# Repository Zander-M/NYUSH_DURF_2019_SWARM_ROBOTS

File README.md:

# NYUSH_DURF_2019_SWARM_ROBOTS

For project logs, please visit [<https://hackaday.io/project/165119-nyu-shanghai-swarm-robot-systemhackaday.io/>] for project log and other stuff.

Project Code is in the Project/Code/ folder.  
Project Note is in the Project/Note/ folder.

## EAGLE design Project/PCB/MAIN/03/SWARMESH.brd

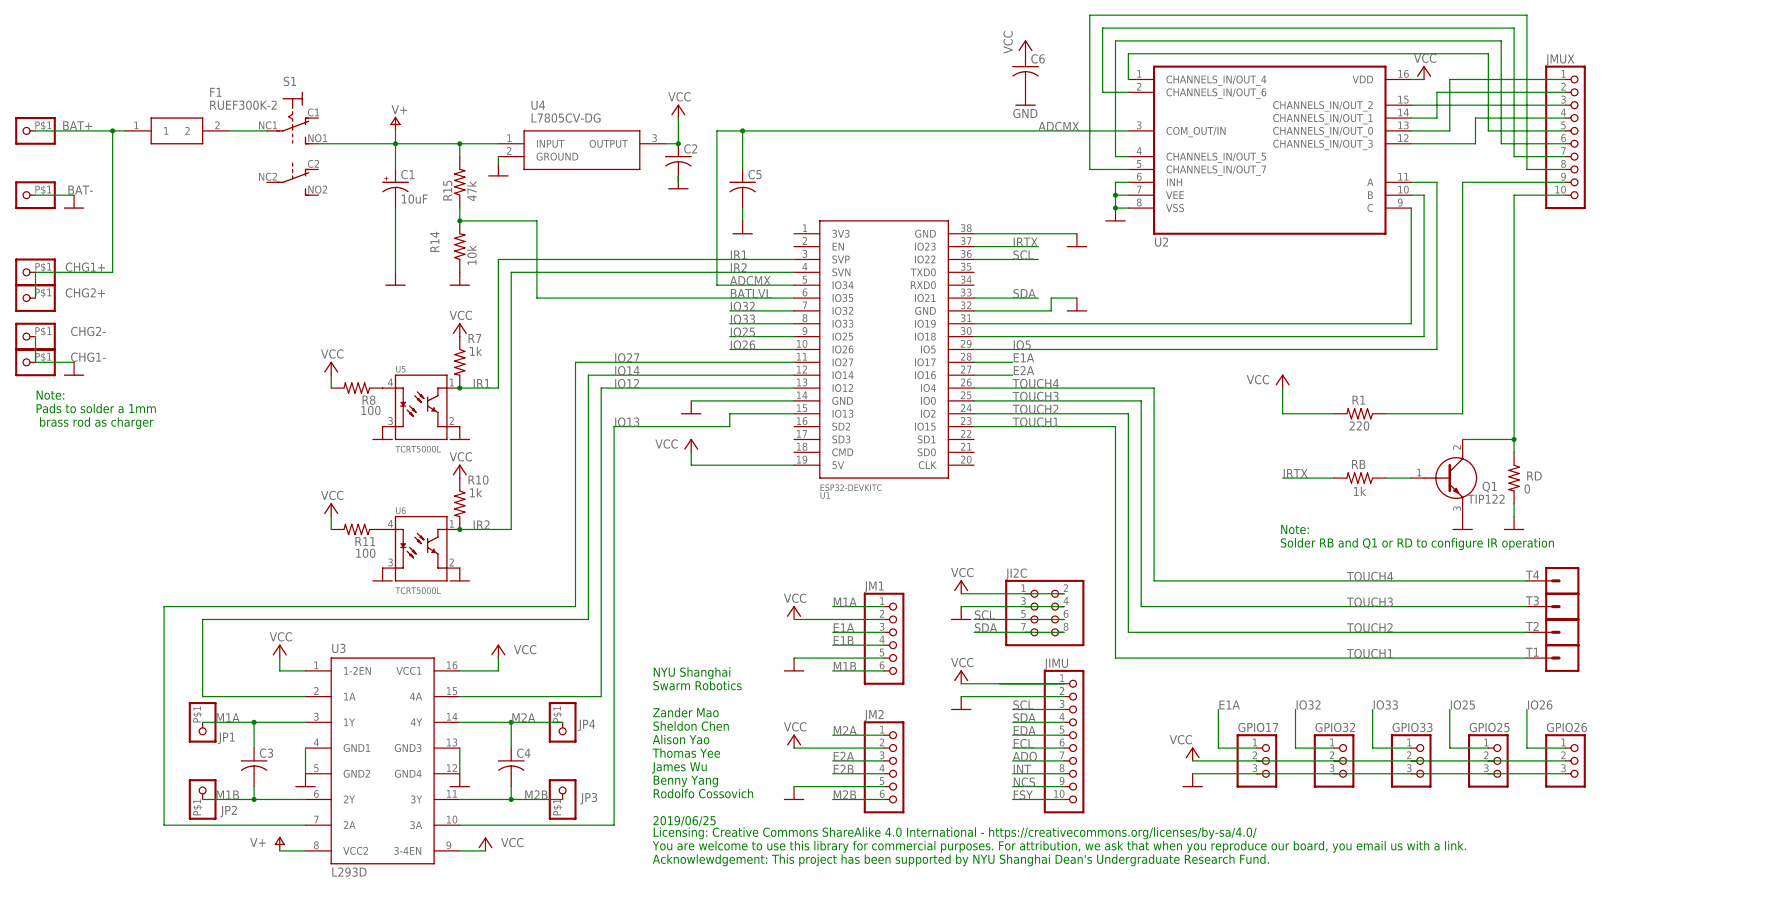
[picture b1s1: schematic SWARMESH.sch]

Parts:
BAT+: PINHD-1X1-BIGPOGO; 1X1-BIGPOGO
BAT-: PINHD-1X1-BIGPOGO; 1X1-BIGPOGO
C1: 10uF; E2-5
C2, C5: C-US025-030X050; C025-030X050
C3, C4, C6: C-US025-025X050; C025-025X050
CHG1+, CHG1-, CHG2+, CHG2-: PINHD-1X1-BIGPOGO; 1X1-BIGPOGO
F1: RUEF300K-2; RUEF300K2
GPIO17, GPIO25, GPIO26, GPIO32, GPIO33: PINHD-1X3; 1X03
JI2C: PINHD-2X4; 2X04
JIMU: PINHD-1X10; 1X10-BIG
JM1, JM2: PINHD-1X6; 1X06
JMUX: PINHD-1X10; 1X10-BIG
JP1, JP2, JP3, JP4: PINHD-1X1-BIGPOGO; 1X1-BIGPOGO
Q1: TIP122; TO270P460X1020X2008-3P
R1: 220; 0207/9
R7, R10: 1k; 0207/9
R8, R11: 100; 0207/9
R14: 10k; 0207/9
R15: 47k; 0207/9
RB: 1k; 0207/9
RD: 0; 0207/9
S1: SWITCH_320-938; PS22F03
T1, T2, T3, T4: CONN_01SPRING-CONN; SPRING-CONNECTOR
U1: ESP32DEVKITC; ESP32-DEVKITC
U2: CD4051BEE4; CD4051BEE4DIP
U3: L293D; DIL16
U4: L7805CV-DG; TO270P460X1020X2008-3P
U5, U6: TCRT5000L; XDCR_TCRT5000L

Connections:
ADCMX: C5.1, U1.5 (IO34), U2.3 (COM_OUT/IN)
ADO: JIMU.7
BATLVL: R14.2, R15.1, U1.6 (IO35)
E1A: GPIO17.1, JM1.3, U1.28 (IO17)
E1B: JM1.4
E2A: JM2.3, U1.27 (IO16)
E2B: JM2.4
ECL: JIMU.6
EDA: JIMU.5
FSY: JIMU.10
GND: BAT-.P$1, C1.-, C2.2, C5.2, C6.2, CHG1-.P$1, CHG2-.P$1, GPIO17.3, GPIO25.3, GPIO26.3, GPIO32.3, GPIO33.3, JI2C.3, JI2C.4, JIMU.2, JM1.5, JM2.5, Q1.3 (E), R14.1, RD.2, U1.14 (GND), U1.32 (GND), U1.38 (GND), U3.4 (GND1), U3.5 (GND2), U3.12 (GND4), U3.13 (GND3), U4.2 (GROUND), U5.2 (E), U5.3 (C), U6.2 (E), U6.3 (C)
INT: JIMU.8
IO5: U1.29 (IO5), U2.11 (A)
IO12: U1.13 (IO12), U3.15 (4A)
IO13: U1.15 (IO13), U3.10 (3A)
IO14: U1.12 (IO14), U3.2 (1A)
IO25: GPIO25.1, U1.9 (IO25)
IO26: GPIO26.1, U1.10 (IO26)
IO27: U1.11 (IO27), U3.7 (2A)
IO32: GPIO32.1, U1.7 (IO32)
IO33: GPIO33.1, U1.8 (IO33)
IR1: R7.2, U1.3 (SVP), U5.1 (CO)
IR2: R10.2, U1.4 (SVN), U6.1 (CO)
IRTX: RB.2, U1.37 (IO23)
M1A: C3.1, JM1.1, JP1.P$1, U3.3 (1Y)
M1B: C3.2, JM1.6, JP2.P$1, U3.6 (2Y)
M2A: C4.1, JM2.1, JP4.P$1, U3.14 (4Y)
M2B: C4.2, JM2.6, JP3.P$1, U3.11 (3Y)
unnamed: JMUX.6, U2.4 (CHANNELS_IN/OUT_5)
unnamed: U1.30 (IO18), U2.10 (B)
unnamed: U1.31 (IO19), U2.9 (C)
unnamed: R11.1, U6.4 (A)
unnamed: R8.1, U5.4 (A)
unnamed: JMUX.5, U2.1 (CHANNELS_IN/OUT_4)
unnamed: Q1.1 (B), RB.1, U2.6 (INH), U2.7 (VEE), U2.8 (VSS)
unnamed: JMUX.7, U2.2 (CHANNELS_IN/OUT_6)
unnamed: JMUX.8, U2.5 (CHANNELS_IN/OUT_7)
unnamed: BAT+.P$1, CHG1+.P$1, CHG2+.P$1, F1.1
unnamed: JMUX.9, R1.1
unnamed: JMUX.10, Q1.2 (C), RD.1
unnamed: F1.2, S1.NC1
unnamed: JMUX.1, U2.13 (CHANNELS_IN/OUT_0)
unnamed: JMUX.2, U2.14 (CHANNELS_IN/OUT_1)
unnamed: JMUX.4, U2.12 (CHANNELS_IN/OUT_3)
unnamed: JMUX.3, U2.15 (CHANNELS_IN/OUT_2)
NCS: JIMU.9
SCL: JI2C.5, JI2C.6, JIMU.3, U1.36 (IO22)
SDA: JI2C.7, JI2C.8, JIMU.4, U1.33 (IO21)
TOUCH1: T1.P$2, U1.23 (IO15)
TOUCH2: T2.P$2, U1.24 (IO2)
TOUCH3: T3.P$2, U1.25 (IO0)
TOUCH4: T4.P$2, U1.26 (IO4)
V+: C1.+, R15.2, S1.NO1 (S), U3.8 (VCC2), U4.1 (INPUT)
VCC: C2.1, C6.1, GPIO17.2, GPIO25.2, GPIO26.2, GPIO32.2, GPIO33.2, JI2C.1, JI2C.2, JIMU.1, JM1.2, JM2.2, R1.2, R7.1, R8.2, R10.1, R11.2, U1.19 (5V), U2.16 (VDD), U3.1 (1-2EN), U3.9 (3-4EN), U3.16 (VCC1), U4.3 (OUTPUT)

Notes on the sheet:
NYU Shanghai Swarm Robotics Zander Mao Sheldon Chen Alison Yao Thomas Yee James Wu Benny Yang Rodolfo Cossovich 2019/06/25
Licensing: Creative Commons ShareAlike 4.0 International - https://creativecommons.org/licenses/by-sa/4.0/ You are welcome to use this library for commercial purposes. For attribution, we ask that when you reproduce our board, you email us with a link. Acknowlewdgement: This project has been suppor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
Note: Solder RB and Q1 or RD to configure IR operation
Note: Pads to solder a 1mm brass rod as charger

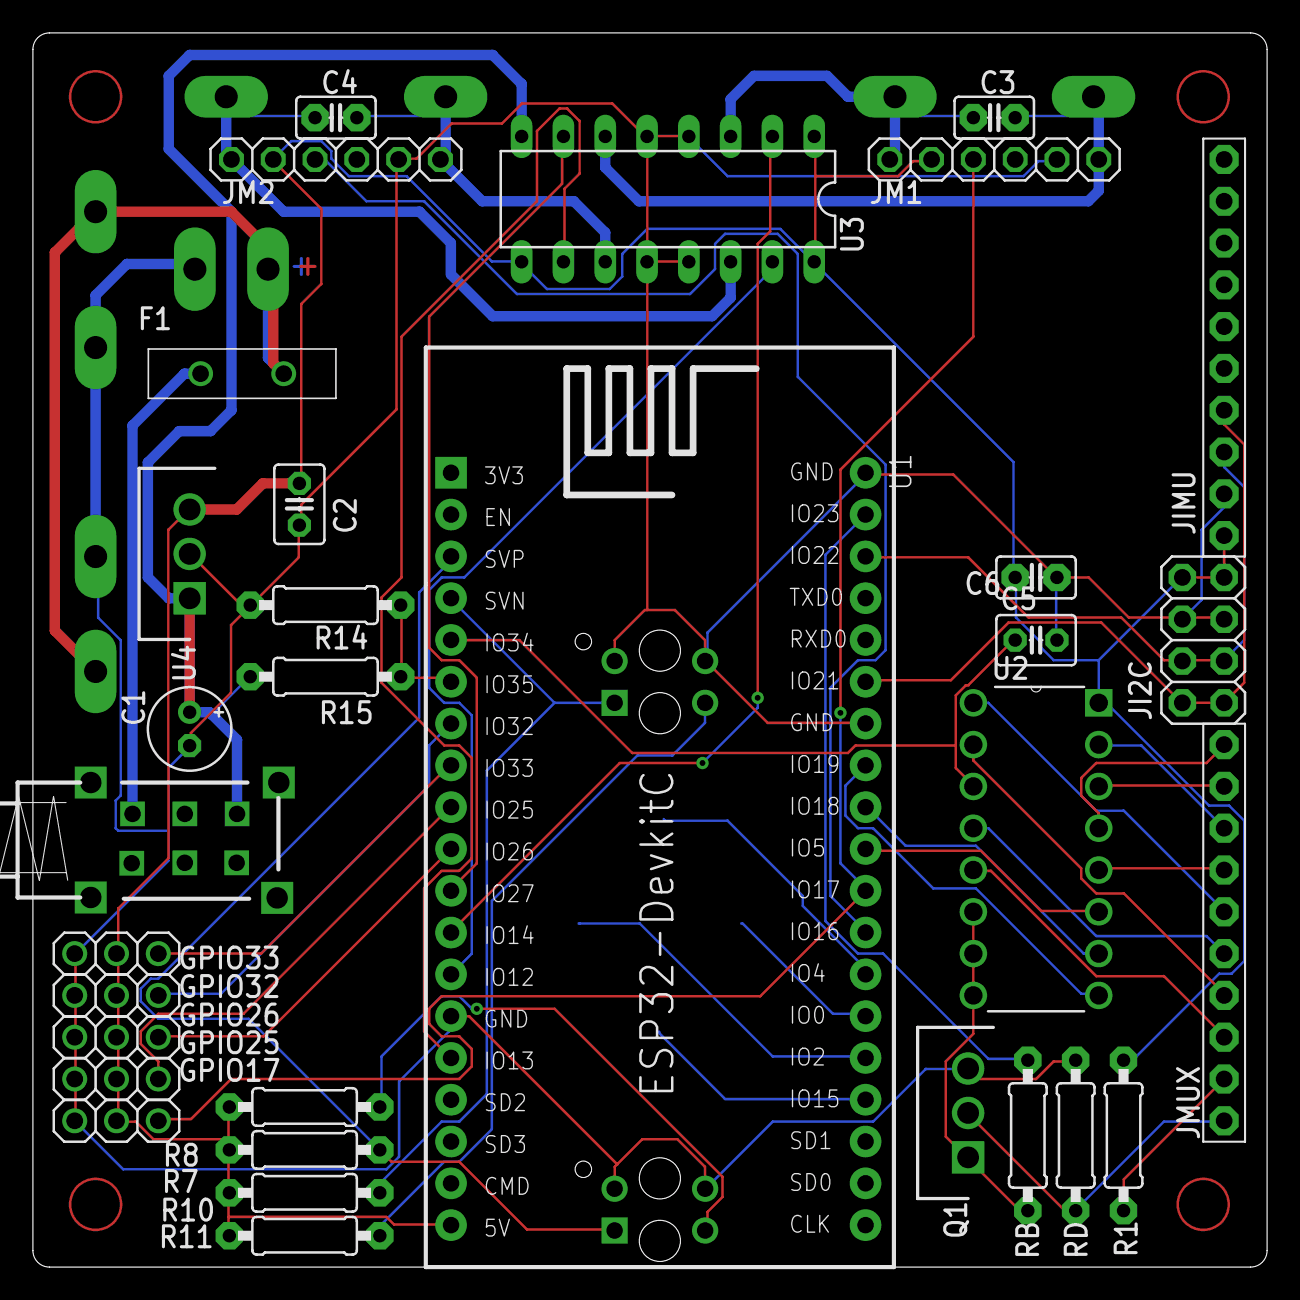
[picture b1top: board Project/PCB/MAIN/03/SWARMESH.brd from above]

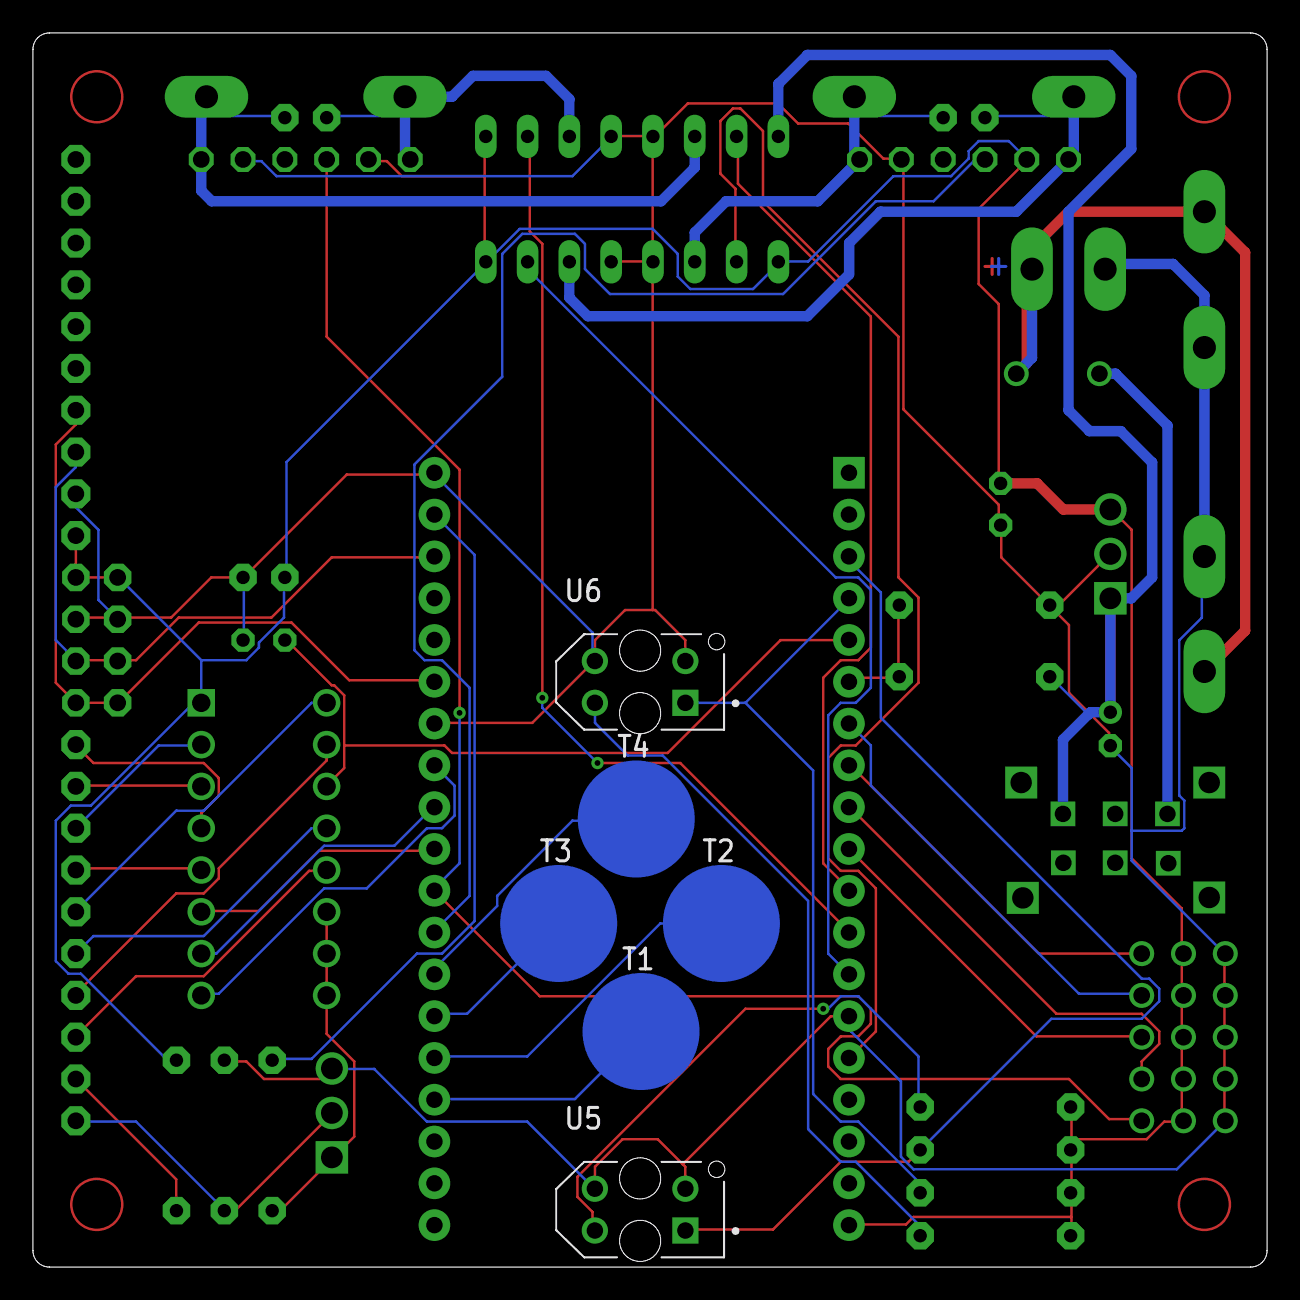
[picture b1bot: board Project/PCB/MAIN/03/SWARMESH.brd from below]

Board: 2 copper layers, 75.0 x 75.0 mm, 48 parts (7 on the bottom side), 46 nets.

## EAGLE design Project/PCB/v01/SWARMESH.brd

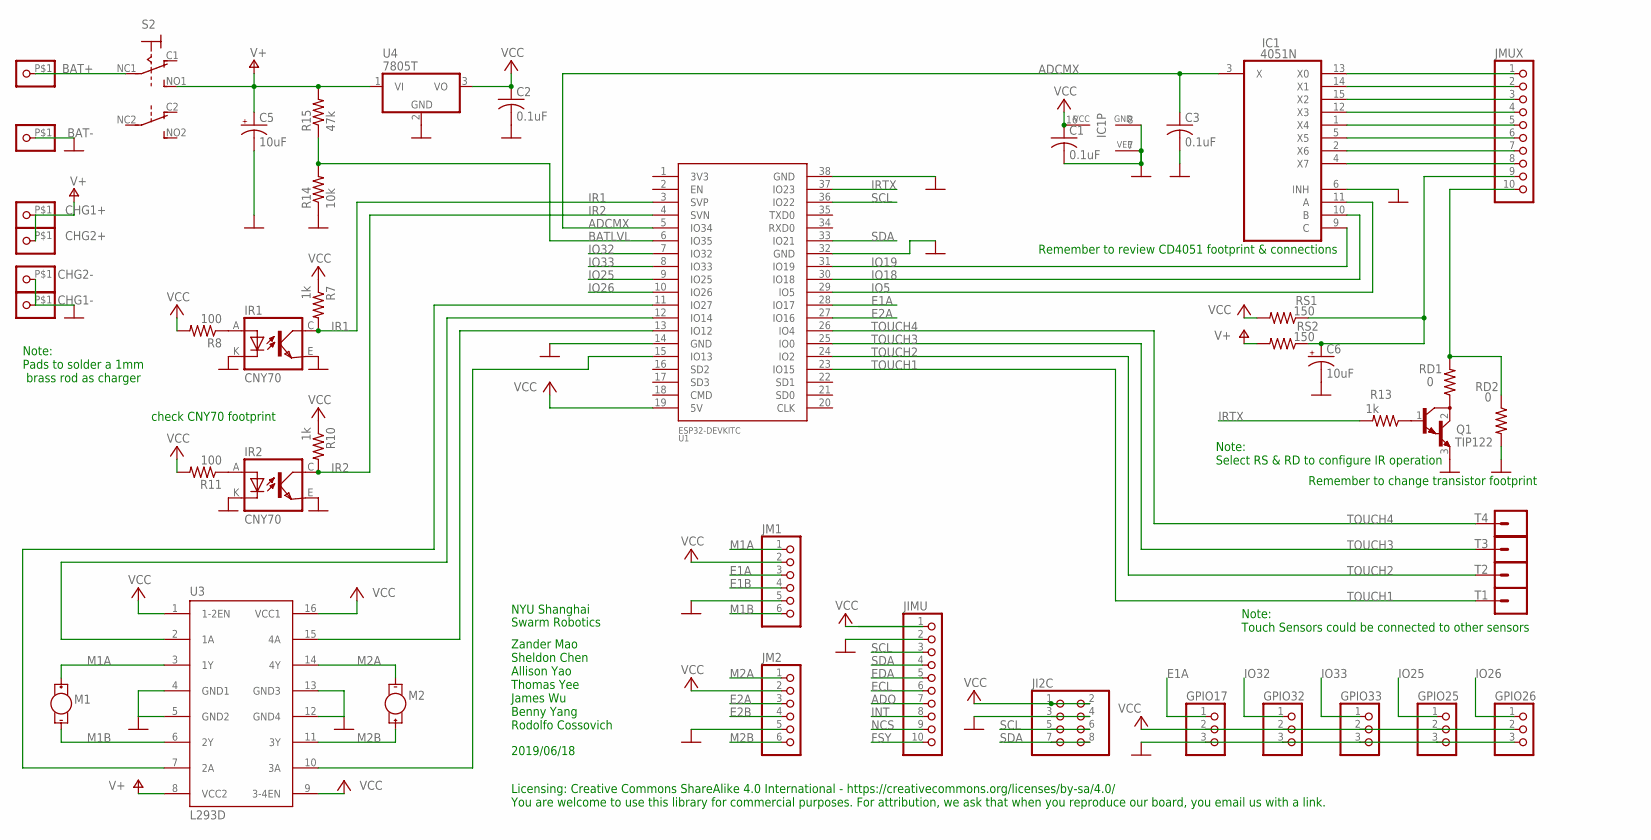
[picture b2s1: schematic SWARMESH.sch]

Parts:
BAT+: PINHD-1X1-BIGPOGO; 1X1-BIGPOGO
BAT-: PINHD-1X1-BIGPOGO; 1X1-BIGPOGO
C1, C2, C3: 0.1uF; C050-024X044
C5, C6: 10uF; E2,5-7
CHG1+, CHG1-, CHG2+, CHG2-: PINHD-1X1-BIGPOGO; 1X1-BIGPOGO
GPIO17, GPIO25, GPIO26, GPIO32, GPIO33: PINHD-1X3; 1X03
IC1: 4051N; DIL16
IR1, IR2: CNY70; 4
JI2C: PINHD-2X4; 2X04
JIMU: PINHD-1X10; 1X10-BIG
JM1, JM2: PINHD-1X6; 1X06
JMUX: PINHD-1X10; 1X10-BIG
M1, M2: MOTOR10MM; VIBE-MOTOR-10MM
Q1: TIP122; TO220
R7, R10, R13: 1k; 0207/12
R8, R11: 100; 0207/12
R14: 10k; 0207/12
R15: 47k; 0207/12
RD1, RD2: 0; 0207/12
RS1, RS2: 150; 0207/12
S2: SWITCH_320-938; PS22F03
T1, T2, T3, T4: CONN_01SPRING-CONN; SPRING-CONNECTOR
U1: ESP32DEVKITC; ESP32-DEVKITC
U3: L293D; DIL16
U4: 7805T; TO220H

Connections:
ADCMX: C3.1, IC1.3 (X), U1.5 (IO34)
ADO: JIMU.7
BATLVL: R14.2, R15.1, U1.6 (IO35)
E1A: GPIO17.1, JM1.3, U1.28 (IO17)
E1B: JM1.4
E2A: JM2.3, U1.27 (IO16)
E2B: JM2.4
ECL: JIMU.6
EDA: JIMU.5
FSY: JIMU.10
GND: BAT-.P$1, C1.2, C2.2, C3.2, C5.-, C6.-, CHG1-.P$1, CHG2-.P$1, GPIO17.3, GPIO25.3, GPIO26.3, GPIO32.3, GPIO33.3, IC1.6 (INH), IC1.7 (VEE), IC1.8 (GND), IR1.E (EMI), IR1.K (C), IR2.E (EMI), IR2.K (C), JI2C.3, JI2C.4, JIMU.2, JM1.5, JM2.5, Q1.3 (E), R14.1, RD2.2, U1.14 (GND), U1.32 (GND), U1.38 (GND), U3.4 (GND1), U3.5 (GND2), U3.12 (GND4), U3.13 (GND3), U4.2 (GND)
INT: JIMU.8
IO5: IC1.11 (A), U1.11 (IO27), U1.12 (IO14), U1.13 (IO12), U1.15 (IO13), U1.29 (IO5), U3.2 (1A), U3.7 (2A), U3.10 (3A), U3.15 (4A)
IO18: IC1.10 (B), U1.30 (IO18)
IO19: IC1.9 (C), U1.31 (IO19)
IO25: GPIO25.1, U1.9 (IO25)
IO26: GPIO26.1, U1.10 (IO26)
IO32: GPIO32.1, U1.7 (IO32)
IO33: GPIO33.1, U1.8 (IO33)
IR1: IR1.C (COL), R7.2, U1.3 (SVP)
IR2: IR2.C (COL), R10.2, U1.4 (SVN)
IRTX: R13.2, U1.37 (IO23)
M1A: JM1.1, M1.+, U3.3 (1Y)
M1B: JM1.6, M1.-, U3.6 (2Y)
M2A: JM2.1, M2.-, U3.14 (4Y)
M2B: JM2.6, M2.+, U3.11 (3Y)
unnamed: Q1.1 (B), R13.1
unnamed: IC1.13 (X0), JMUX.1
unnamed: IC1.14 (X1), JMUX.2
unnamed: IC1.15 (X2), JMUX.3
unnamed: IC1.12 (X3), JMUX.4
unnamed: IC1.1 (X4), JMUX.5
unnamed: IC1.5 (X5), JMUX.6
unnamed: IC1.2 (X6), JMUX.7
unnamed: IC1.4 (X7), JMUX.8
unnamed: C6.+, JMUX.9, RS1.1, RS2.1
unnamed: JMUX.10, RD1.2, RD2.1
unnamed: IR2.A, R11.1
unnamed: BAT+.P$1, S2.NC1
unnamed: IR1.A, R8.1
unnamed: Q1.2 (C), RD1.1
NCS: JIMU.9
SCL: JI2C.5, JI2C.6, JIMU.3, U1.36 (IO22)
SDA: JI2C.7, JI2C.8, JIMU.4, U1.33 (IO21)
TOUCH1: T1.P$2, U1.23 (IO15)
TOUCH2: T2.P$2, U1.24 (IO2)
TOUCH3: T3.P$2, U1.25 (IO0)
TOUCH4: T4.P$2, U1.26 (IO4)
V+: C5.+, CHG1+.P$1, CHG2+.P$1, RS2.2, S2.NO1 (S), U3.8 (VCC2), U4.1 (VI)
VCC: C1.1, C2.1, GPIO17.2, GPIO25.2, GPIO26.2, GPIO32.2, GPIO33.2, IC1.16 (VCC), JI2C.1, JI2C.2, JIMU.1, JM1.2, JM2.2, R7.1, R8.2, R10.1, R11.2, RS1.2, U1.19 (5V), U3.1 (1-2EN), U3.9 (3-4EN), U3.16 (VCC1), U4.3 (VO)

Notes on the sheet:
Swarm Robotics
NYU Shanghai
2019/06/18
Zander Mao Sheldon Chen Allison Yao Thomas Yee James Wu Benny Yang Rodolfo Cossovich
Remember to change transistor footprint
Licensing: Creative Commons ShareAlike 4.0 International - https://creativecommons.org/licenses/by-sa/4.0/ You are welcome to use this library for commercial purposes. For attribution, we ask that when you reproduce our board, you email us with a link.
Remember to review CD4051 footprint & connections
Note: Select RS & RD to configure IR operation
check CNY70 footprint
Note: Pads to solder a 1mm brass rod as charger
Note: Touch Sensors could be connected to other sensors

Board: 2 copper layers, 46 parts (0 on the bottom side), 42 nets, no tracks yet.

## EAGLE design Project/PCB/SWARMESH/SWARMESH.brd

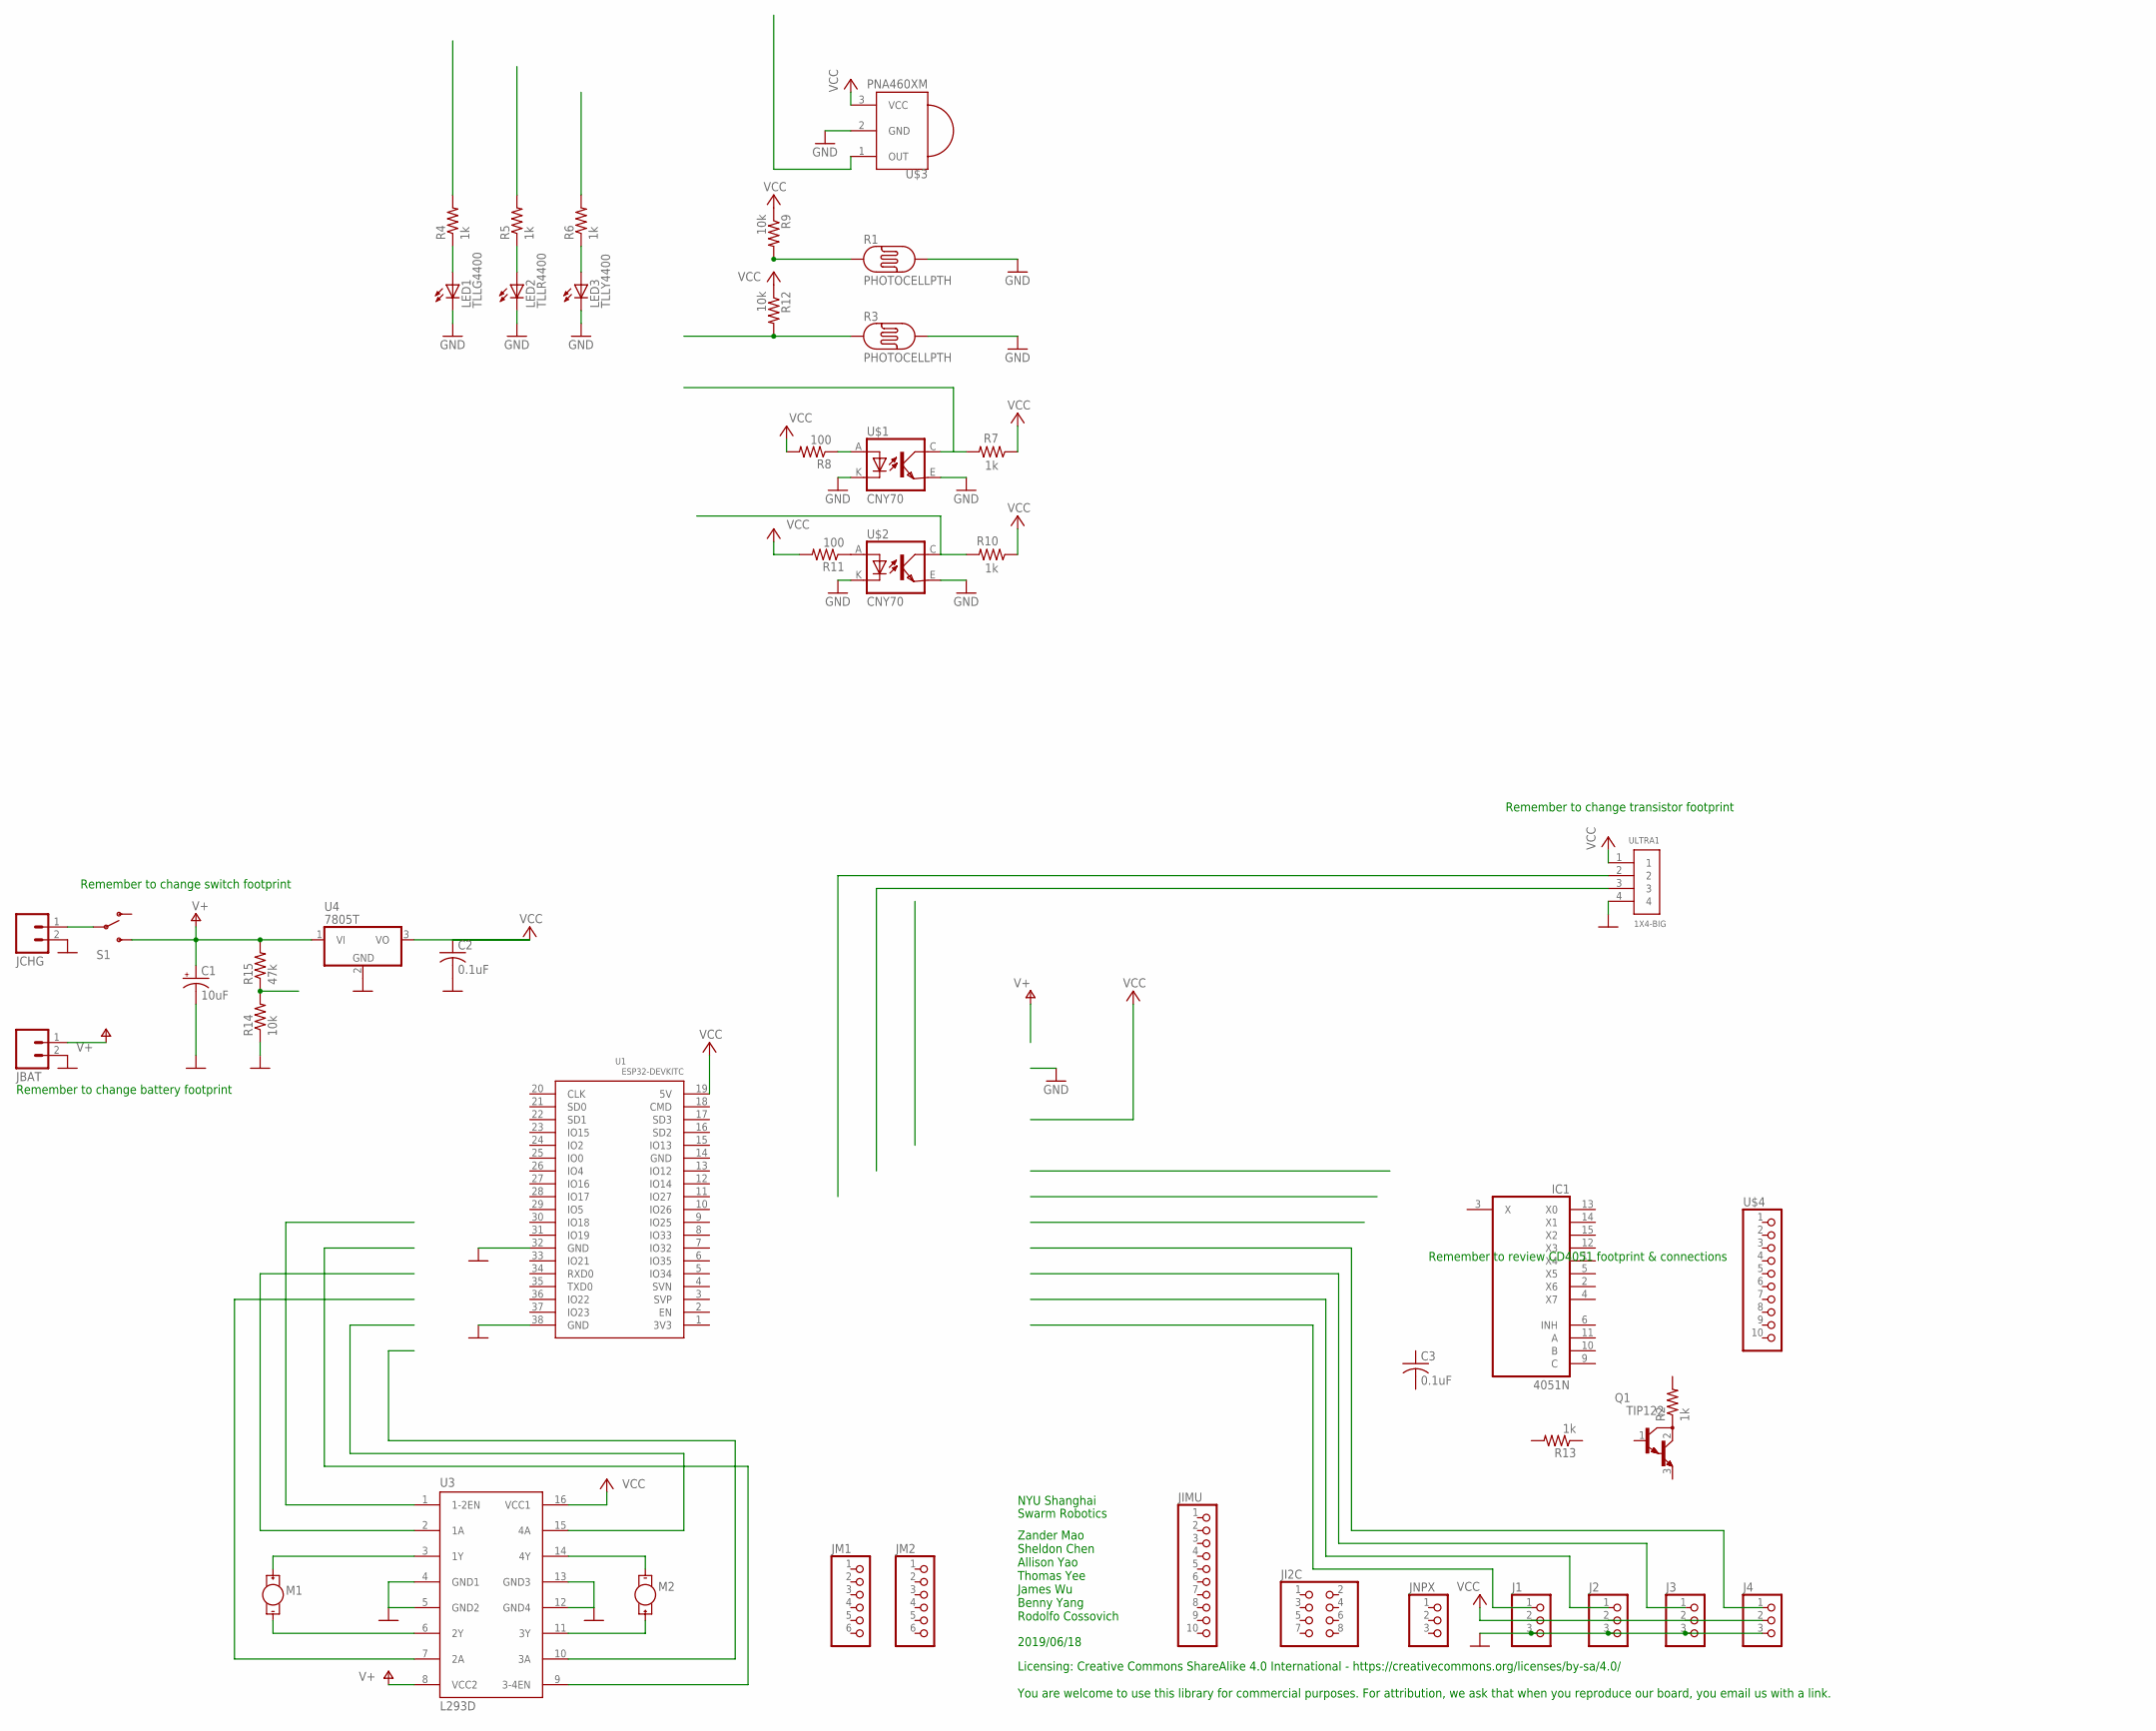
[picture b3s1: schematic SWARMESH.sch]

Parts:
C1: 10uF; EB20D
C2, C3: 0.1uF; C050-024X044
IC1: 4051N; DIL16
J1, J2, J3, J4: PINHD-1X3; 1X03
JBAT: M02-JST-2-PTH-NO_SILK; JST-2-PTH-NS
JCHG: M02-JST-2-PTH-NO_SILK; JST-2-PTH-NS
JI2C: PINHD-2X4; 2X04
JIMU: PINHD-1X10; 1X10-BIG
JM1, JM2: PINHD-1X6; 1X06
JNPX: PINHD-1X3; 1X03
LED1: TLLG4400; LED3MM
LED2: TLLR4400; LED3MM
LED3: TLLY4400; LED3MM
M1, M2: MOTOR10MM; VIBE-MOTOR-10MM
Q1: TIP122; TO220
R1, R3: PHOTOCELLPTH; PHOTOCELL
R2, R4, R5, R6, R7, R10, R13: 1k; 0207/12
R8, R11: 100; 0207/12
R9, R12, R14: 10k; 0207/12
R15: 47k; 0207/12
S1: SWITCH-SPDTPTH2; SWITCHE-DPDT
U1: ESP32DEVKITC; ESP32-DEVKITC
U3: L293D; DIL16
U4: 7805T; TO220H
U$1, U$2: CNY70; 4
U$3: PNA460XM
U$4: PINHD-1X10; 1X10-BIG
ULTRA1: 1X4-BIG; 1X04-BIG

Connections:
GND: C1.-, C2.2, IC1.8 (GND), J1.3, J2.3, J3.3, J4.3, JBAT.2, JCHG.2, LED1.K (C), LED2.K (C), LED3.K (C), R1.2, R3.2, R14.1, U1.32 (GND), U1.38 (GND), U3.4 (GND1), U3.5 (GND2), U3.12 (GND4), U3.13 (GND3), U4.2 (GND), U$1.E (EMI), U$1.K (C), U$2.E (EMI), U$2.K (C), U$3.2 (GND), ULTRA1.4
unnamed: LED1.A, R4.1
unnamed: LED2.A, R5.1
unnamed: LED3.A, R6.1
unnamed: M1.+, U3.3 (1Y)
unnamed: M1.-, U3.6 (2Y)
unnamed: M2.-, U3.14 (4Y)
unnamed: M2.+, U3.11 (3Y)
unnamed: R7.2, U$1.C (COL)
unnamed: R11.1, U$2.A
unnamed: JCHG.1, S1.2
unnamed: R8.1, U$1.A
unnamed: R1.1, R9.2
unnamed: R10.2, U$2.C (COL)
unnamed: R14.2, R15.1
unnamed: R3.1, R12.2
unnamed: Q1.2 (C), R2.1
V+: C1.+, JBAT.1, S1.3 (S), U3.8 (VCC2), U4.1 (VI)
VCC: C2.1, IC1.16 (VCC), J1.2, J2.2, J3.2, J4.2, R7.1, R8.2, R9.1, R10.1, R11.2, R12.1, U1.19 (5V), U3.16 (VCC1), U4.3 (VO), U$3.3 (VCC), ULTRA1.1
VEE: IC1.7 (VEE)

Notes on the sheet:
Swarm Robotics
NYU Shanghai
Remember to change battery footprint
2019/06/18
Zander Mao Sheldon Chen Allison Yao Thomas Yee James Wu Benny Yang Rodolfo Cossovich
Remember to change switch footprint
Remember to change transistor footprint
Licensing: Creative Commons ShareAlike 4.0 International - https://creativecommons.org/licenses/by-sa/4.0/ You are welcome to use this library for commercial purposes. For attribution, we ask that when you reproduce our board, you email us with a link.
Remember to review CD4051 footprint & connections

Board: 2 copper layers, 45 parts (0 on the bottom side), 19 nets, no tracks yet.

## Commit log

2019-04-18 adding blog folder
2019-04-18 rename it to docs as requested...
2019-04-18 Set theme jekyll-theme-slate
2019-04-18 add jekyll
2019-04-18 modified _config.yml
2019-04-18 modified pages description
2019-06-06 wifi mesh added
2019-06-06 update MCPWM
2019-06-06 add project template
2019-06-06 update README& git ignore
2019-06-06 remove some file
2019-06-06 remove ws file
2019-06-09 add uart test & mesh test
2019-06-12 setup uart queue
2019-06-14 fixed xQueueSend Bug
2019-06-14 mesh control done
2019-06-14 add brief note
2019-06-18 added pcb
2019-06-18 added sch
2019-06-18 deleting stray file
2019-06-18 updated name and deleted unnecessary components
2019-06-18 removed directory
2019-06-18 added datasheets
2019-06-18 added CNY70 & touch sensors
2019-06-18 first revision
2019-06-19 reorganized PCB folder. Components Lib and Docs are now in the sub folders of PCB.\ Add v01/02, changed CD4051 to pin definition. Changed CNY70 to TCRT5000L. Need to be compiled. Docs are not complet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
2019-06-23 update schematic
2019-06-23 minor update
2019-06-23 second minor update
2019-06-25 add led PCB
2019-06-25 ESP-IDF with arduino FastLED lib in Arduino_IDF folder
2019-06-26 component placement
2019-06-26 tested with autorouting
2019-07-18 update&finish multiplexer test
2019-07-18 restructure motor test
2019-07-18 compile file
2019-07-18 update motor test (with circuit board)
2019-07-20 update win file
2019-07-21 ignore build files
2019-07-21 clean build
2019-07-23 started v3 of PCB
2019-07-24 added power net to PCB, corrected orphan GND network in SCH
2019-07-24 added comments
2019-07-28 routing complete - unchecked
2019-07-30 update brd
2019-07-30 update pcb 20:33
2019-09-16 added 2nd version of IR pcb
2019-09-17 modified tracks IR pcb
2019-09-17 modified tracks IR pcb2
2021-07-13 Bump addressable from 2.6.0 to 2.8.0 in /docs
    Bumps [addressable](https://github.com/sporkmonger/addressable) from 2.6.0 to 2.8.0.
    - [Release notes](https://github.com/sporkmonger/addressable/releases)
    - [Changelog](https://github.com/sporkmonger/addressable/blob/main/CHANGELOG.md)
    - [Commits](https://github.com/sporkmonger/addressable/compare/addressable-2.6.0...addressable-2.8.0)
    ---
    updated-dependencies:
2022-10-06 Bump addressable from 2.6.0 to 2.8.1 in /docs
    Bumps [addressable](https://github.com/sporkmonger/addressable) from 2.6.0 to 2.8.1.
    - [Release notes](https://github.com/sporkmonger/addressable/releases)
    - [Changelog](https://github.com/sporkmonger/addressable/blob/main/CHANGELOG.md)
    - [Commits](https://github.com/sporkmonger/addressable/compare/addressable-2.6.0...addressable-2.8.1)
    ---
    updated-dependencies:
2026-04-08 Bump addressable from 2.6.0 to 2.9.0 in /docs
    Bumps [addressable](https://github.com/sporkmonger/addressable) from 2.6.0 to 2.9.0.
    - [Changelog](https://github.com/sporkmonger/addressable/blob/main/CHANGELOG.md)
    - [Commits](https://github.com/sporkmonger/addressable/compare/addressable-2.6.0...addressable-2.9.0)
    ---
    updated-dependencies:
    - dependency-name: addressable
2026-06-23 Bump concurrent-ruby from 1.1.5 to 1.3.7 in /docs
    Bumps [concurrent-ruby](https://github.com/ruby-concurrency/concurrent-ruby) from 1.1.5 to 1.3.7.
    - [Release notes](https://github.com/ruby-concurrency/concurrent-ruby/releases)
    - [Changelog](https://github.com/ruby-concurrency/concurrent-ruby/blob/master/CHANGELOG.md)
    - [Commits](https://github.com/ruby-concurrency/concurrent-ruby/compare/v1.1.5...v1.3.7)
    ---
    updated-dependencies:
